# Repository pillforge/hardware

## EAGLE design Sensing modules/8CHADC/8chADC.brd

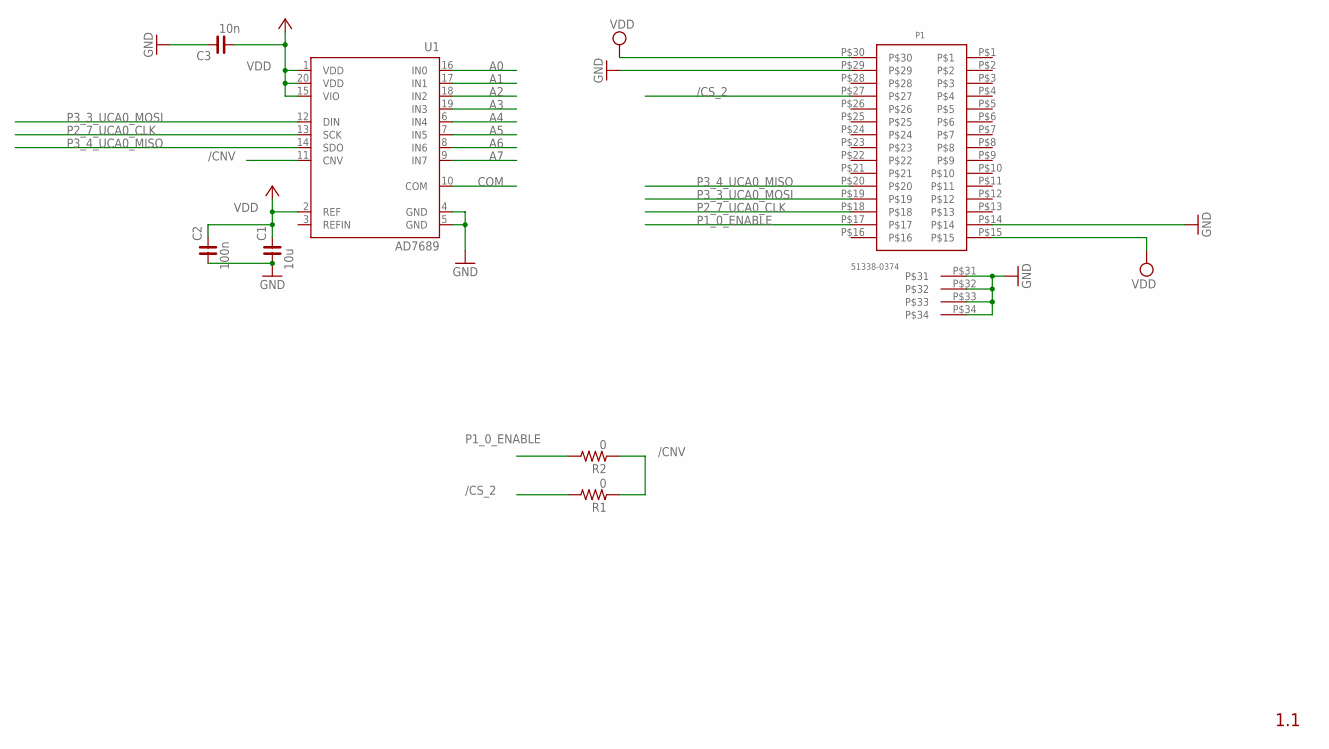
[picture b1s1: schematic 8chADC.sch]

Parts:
C1: 10u; C0402
C2: 100n; C0402
C3: 10n; C0402
P1: 51338-0374; 51338-0374_RECEPTACLE
R1, R2: 0; R0402
U1: AD7689; LFCSP20

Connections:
/CNV: R1.1, R2.1, U1.11 (CNV)
/CS_2: P1.P$27, R1.2
A0: U1.16 (IN0)
A1: U1.17 (IN1)
A2: U1.18 (IN2)
A3: U1.19 (IN3)
A4: U1.6 (IN4)
A5: U1.7 (IN5)
A6: U1.8 (IN6)
A7: U1.9 (IN7)
COM: U1.10 (COM)
GND: C1.1, C2.1, C3.2, P1.P$14, P1.P$29, P1.P$31, P1.P$32, P1.P$33, P1.P$34, U1.4 (GND), U1.5 (GND)
P1_0_ENABLE: P1.P$17, R2.2
P2_7_UCA0_CLK: P1.P$18, U1.13 (SCK)
P3_3_UCA0_MOSI: P1.P$19, U1.12 (DIN)
P3_4_UCA0_MISO: P1.P$20, U1.14 (SDO)
VDD: C1.2, C2.2, C3.1, P1.P$15, P1.P$30, U1.1 (VDD), U1.2 (REF), U1.15 (VIO), U1.20 (VDD)

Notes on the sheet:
1.1

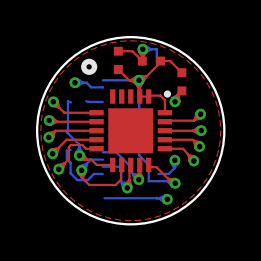
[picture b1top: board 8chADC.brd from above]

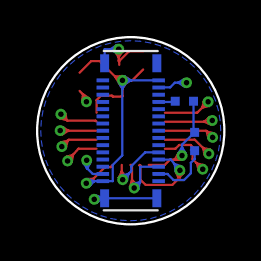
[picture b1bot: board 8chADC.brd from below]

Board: 2 copper layers, 10.4 x 10.4 mm, 7 parts (3 on the bottom side), 8 nets.

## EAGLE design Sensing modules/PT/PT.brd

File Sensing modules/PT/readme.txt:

XXXXXXXXXXXXXXXXXXXXXXXXXXXXXXXXXXXXXXXXXXXXXXXXXXXXXXXXXXXXXXXXXXXXXXXXXXXXX
X                                                                           X
X   Artwork and documentation done by: STORM LAB                            X
X                                                                           X
X   Company: VANDERBILT UNIVERSITY                                          X
XXXXXXXXXXXXXXXXXXXXXXXXXXXXXXXXXXXXXXXXXXXXXXXXXXXXXXXXXXXXXXXXXXXXXXXXXXXXX

PROJECT : PT
PCB NAME : PT
REVISION: 1.1 
DATE: 4-28-2015

PCB DESCRIPTION: 2 LAYER PCB 0.8 MM NOMINAL THICKNESS FR4
		Dimensions in mil (0.001 inch)
                            DOUBLE SIDE SOLDER MASK,
                            DOUBLE SIDE SILKSCREEN,
                            6 MIL MIN TRACE WIDTH AND 6 MIL MIN ISOLATION
		Dielectric constant for FR4 is 4.5

FILE NAME            		DESCRIPTION                               	FILE TYPE
-------------------------------------------------------------------------------------------
***PCB MANUFACTURING FILES:
PT.cmp				LAYER 1 COMPONENT SIDE/POSITIV              EXT. GERBER
PT.sol				LAYER 2 Inner layer/POSITIV                 EXT. GERBER

PT.stc				SOLDER MASK COMPONENT SIDE/NEGATIVE         EXT. GERBER
PT.stl				SOLDER MASK SOLDER SIDE/NEGATIVE            EXT. GERBER

PT.plc				SILKSCREEN COMPONENT SIDE/POSITIVE          EXT. GERBER
PT.pls				SILKSCREEN SOLDER SIDE/POSITIVE             EXT. GERBER

PT.crc				SOLDER PAST COMPONENT SIDE/POSITIVE         EXT. GERBER
PT.crs				SOLDER PAST SOLDER SIDE/POSITIVE            EXT. GERBER

PT.drd				DRILL/MECHANICAL DRAWING                    EXT. GERBER
PT.dri				DRILL/NC DRILL REPORT                       ASCII
PT.dim				BOARD OUTLINE             		    EXT. GERBER

PT_partlist.xls		PART LIST					    ASCII

***PDF FILES:
PT.PDF	Circuit Diagram

***EAGLE  FILES:
PT.SCH			Eagle 6.6 Schematic file
PT.BRD			Eagle 6.6 Layout file

README.TXT              THIS FILE                                   ASCII

***REVISION HISTORY

none

END.

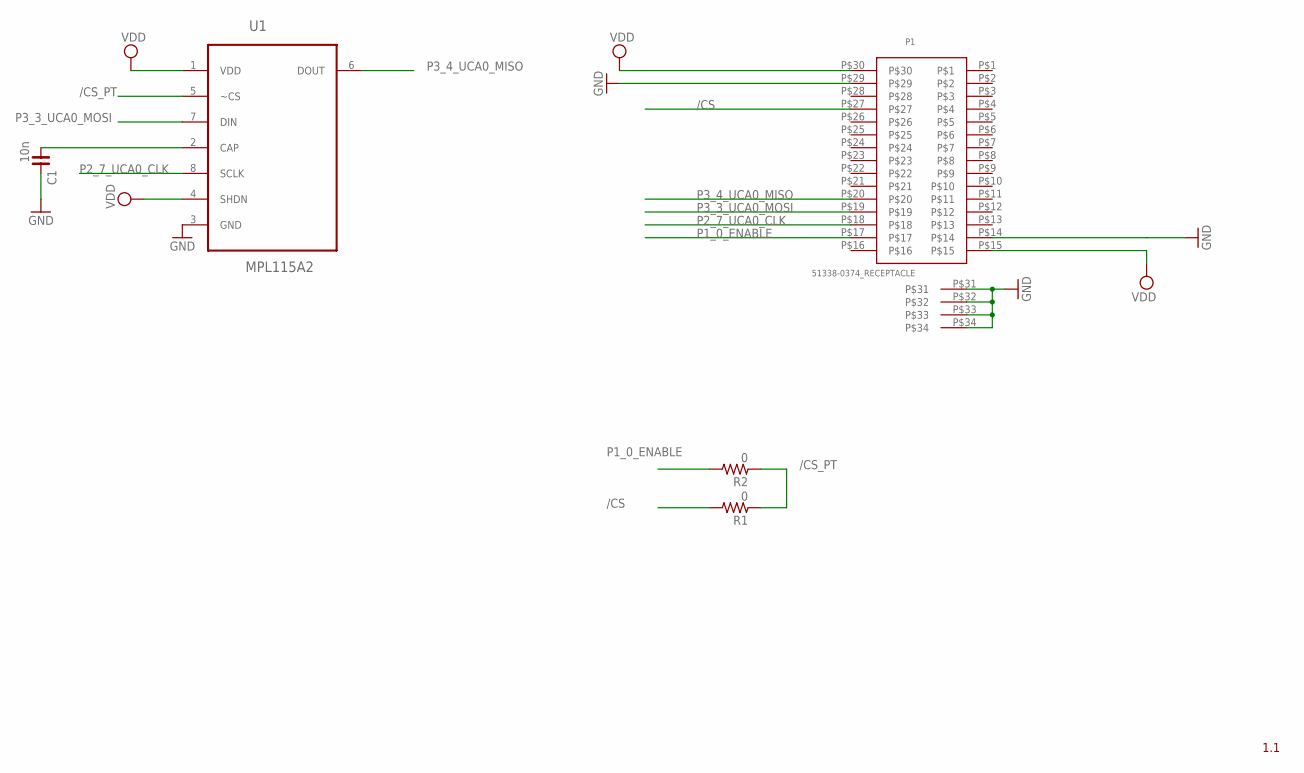
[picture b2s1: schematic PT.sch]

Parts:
C1: 10n; C0402
P1: 51338-0374_RECEPTACLE
R1, R2: 0; R0402
U1: MPL115A2; LGA8R125P0X4_500X300X120

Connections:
/CS: P1.P$27, R1.2
/CS_PT: R1.1, R2.1, U1.5 (~CS)
GND: C1.2, P1.P$14, P1.P$29, P1.P$31, P1.P$32, P1.P$33, P1.P$34, U1.3 (GND)
unnamed: C1.1, U1.2 (CAP)
P1_0_ENABLE: P1.P$17, R2.2
P2_7_UCA0_CLK: P1.P$18, U1.8 (SCLK)
P3_3_UCA0_MOSI: P1.P$19, U1.7 (DIN)
P3_4_UCA0_MISO: P1.P$20, U1.6 (DOUT)
VDD: P1.P$15, P1.P$30, U1.1 (VDD), U1.4 (SHDN)

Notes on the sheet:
1.1

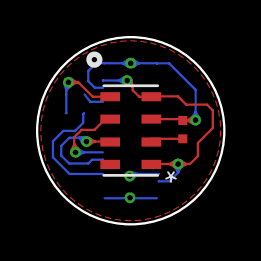
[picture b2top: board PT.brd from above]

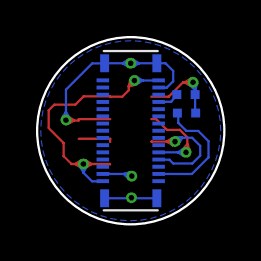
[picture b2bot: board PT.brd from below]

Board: 2 copper layers, 10.4 x 10.4 mm, 5 parts (3 on the bottom side), 9 nets.

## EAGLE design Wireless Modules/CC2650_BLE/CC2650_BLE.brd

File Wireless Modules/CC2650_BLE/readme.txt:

XXXXXXXXXXXXXXXXXXXXXXXXXXXXXXXXXXXXXXXXXXXXXXXXXXXXXXXXXXXXXXXXXXXXXXXXXXXXX
X                                                                           X
X   Artwork and documentation done by: STORM LAB                            X
X                                                                           X
X   Company: VANDERBILT UNIVERSITY                                          X
XXXXXXXXXXXXXXXXXXXXXXXXXXXXXXXXXXXXXXXXXXXXXXXXXXXXXXXXXXXXXXXXXXXXXXXXXXXXX

PROJECT : CC2650_BLE
PCB NAME : CC2650_BLE
REVISION: 1.1 
DATE: 4-28-2015

PCB DESCRIPTION: 2 LAYER PCB 0.8 MM NOMINAL THICKNESS FR4
		Dimensions in mil (0.001 inch)
                            DOUBLE SIDE SOLDER MASK,
                            DOUBLE SIDE SILKSCREEN,
                            6 MIL MIN TRACE WIDTH AND 6 MIL MIN ISOLATION
		Dielectric constant for FR4 is 4.5

FILE NAME            		DESCRIPTION                               	FILE TYPE
-------------------------------------------------------------------------------------------
***PCB MANUFACTURING FILES:
CC2650_BLE.cmp				LAYER 1 COMPONENT SIDE/POSITIV              EXT. GERBER
CC2650_BLE.sol				LAYER 2 Inner layer/POSITIV                 EXT. GERBER

CC2650_BLE.stc				SOLDER MASK COMPONENT SIDE/NEGATIVE         EXT. GERBER
CC2650_BLE.stl				SOLDER MASK SOLDER SIDE/NEGATIVE            EXT. GERBER

CC2650_BLE.plc				SILKSCREEN COMPONENT SIDE/POSITIVE          EXT. GERBER
CC2650_BLE.pls				SILKSCREEN SOLDER SIDE/POSITIVE             EXT. GERBER

CC2650_BLE.crc				SOLDER PAST COMPONENT SIDE/POSITIVE         EXT. GERBER
CC2650_BLE.crs				SOLDER PAST SOLDER SIDE/POSITIVE            EXT. GERBER

CC2650_BLE.drd				DRILL/MECHANICAL DRAWING                    EXT. GERBER
CC2650_BLE.dri				DRILL/NC DRILL REPORT                       ASCII

CC2650_BLE.dim				BOARD OUTLINE                      			EXT. GERBER

CC2650_BLE_partlist.xls		PART LIST									ASCII

***PDF FILES:
CC2650_BLE.PDF	Circuit Diagram

***EAGLE  FILES:
CC2650_BLE.SCH			Eagle 6.6 Schematic file
CC2650_BLE.BRD			Eagle 6.6 Layout file

README.TXT              THIS FILE                                   ASCII

***REVISION HISTORY

none

END.

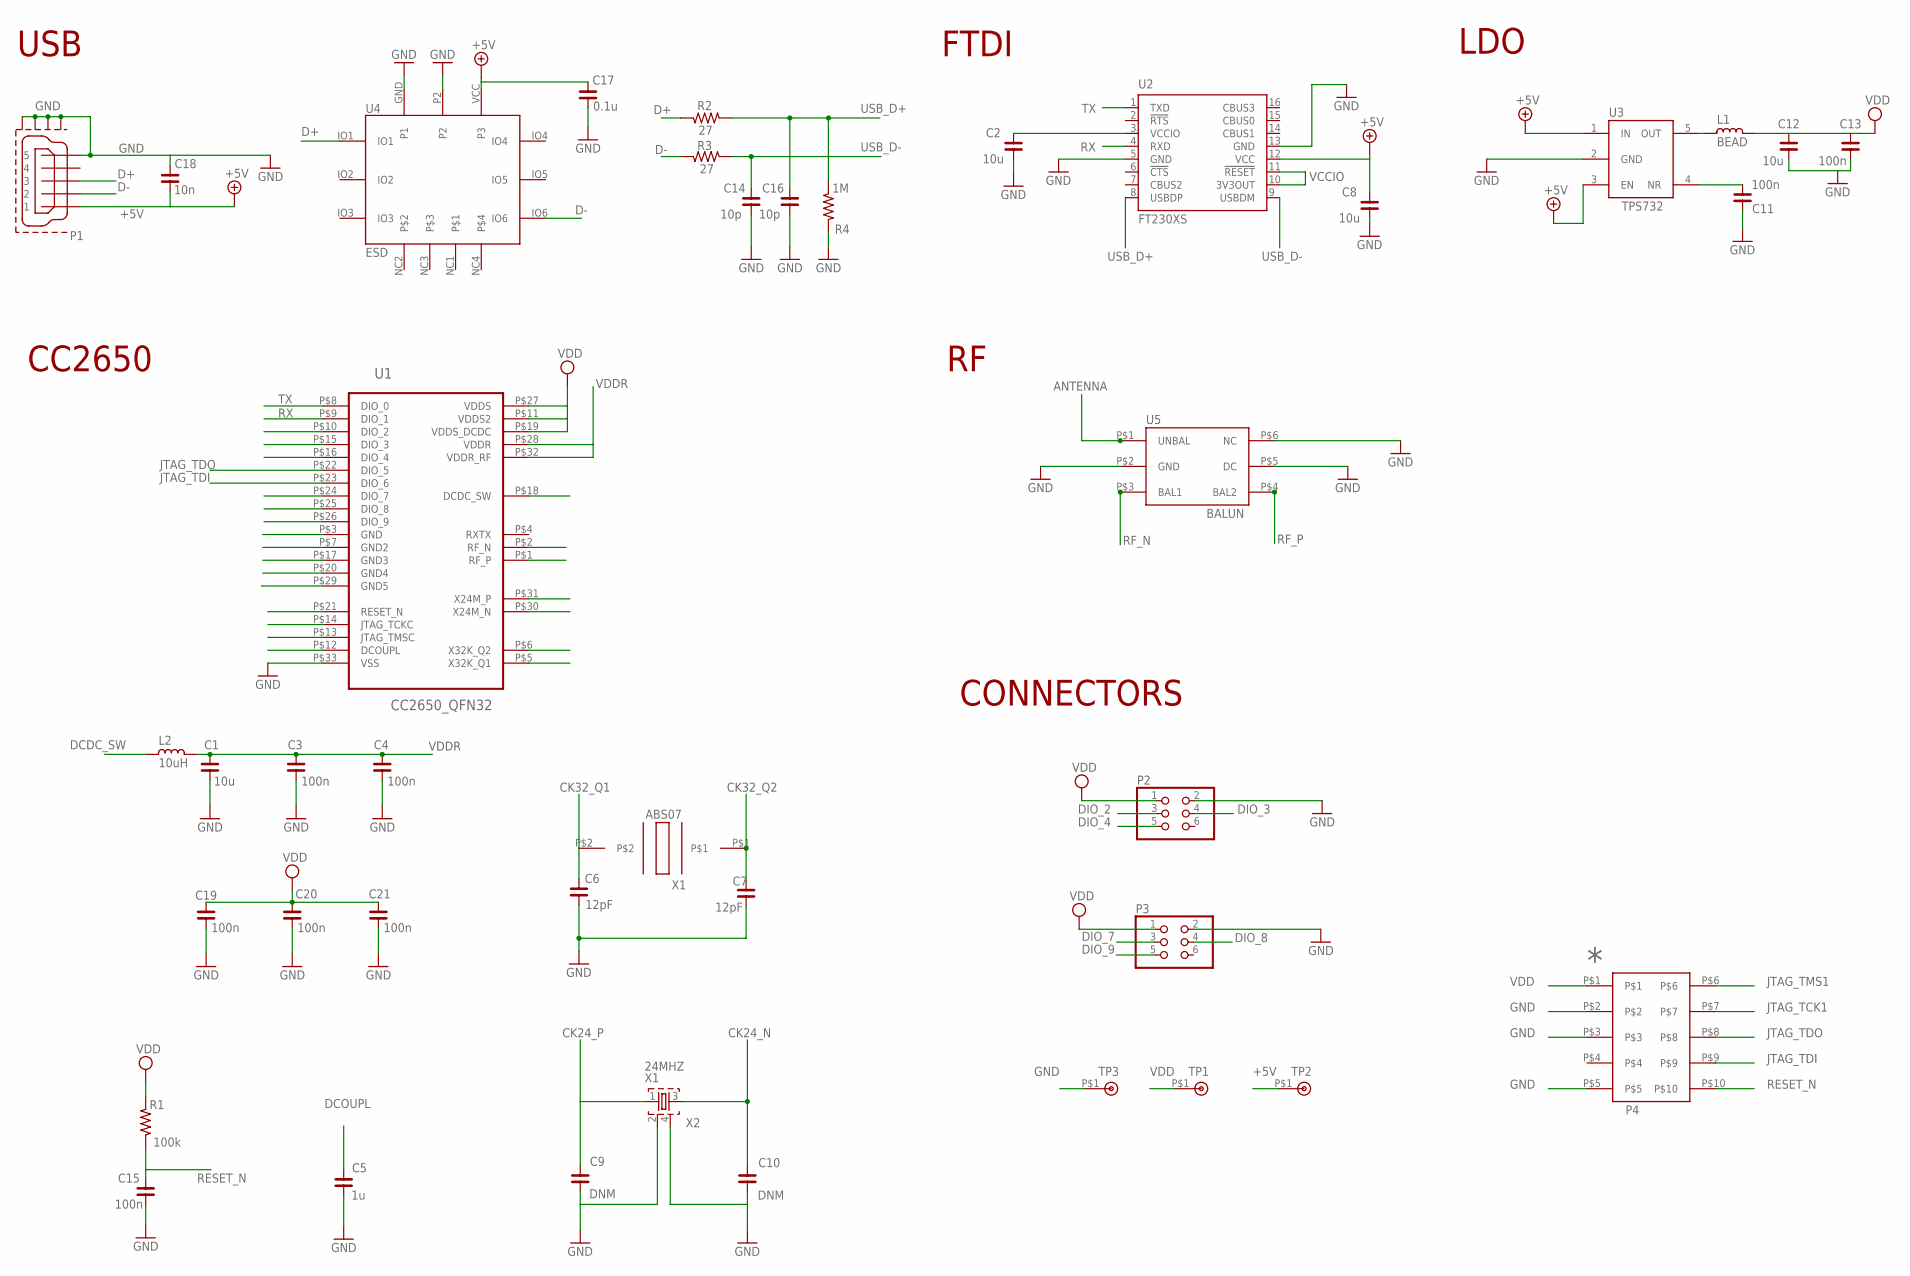
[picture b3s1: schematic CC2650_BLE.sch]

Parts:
24MHZ: X1; FA-20H
32KHZ: OSC32K; ABS07
C1, C2, C8, C12: 10u; C0402
C3, C4, C11, C13, C15, C19, C20, C21: 100n; C0402
C5: 1u; C0402
C6, C7: 12pF; C0402
C9, C10: DNM; C0402
C14, C16: 10p; C0402
C17: 0.1u; C0402
C18: 10n; C0402
L1: BEAD; L0402
L2: 10uH; L0402
P2, P3: PINHD-2X3; 2X03
R1: 100k; R0603
R2, R3: 27; R0603
R4: 1M; R0603
TP1: VDD; 5019_PAD
TP2: +5V; 5019_PAD
TP3: GND; 5019_PAD
U2: FT230XS; SSOP16
U3: TPS732XX; SOT23
U4: ESD
U5: BALUN_NRF8001; BALUNNORDIC
U$3: CC26504X4
U$5: FTSH-105-01-L-DV-K
USB: MINI-USB-SHIELD-UX60-MB-5ST; UX60-MB-5ST

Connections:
+3.3RAW: L1.2, U3.5 (OUT)
+5V: C8.2, C17.2, C18.1, TP2.P$1, U2.12 (VCC), U3.1 (IN), U3.3 (EN), U4.VCC (P3), USB.1
CK24_N: 24MHZ.3, C10.1, U$3.P$30 (X24M_N)
CK24_P: 24MHZ.1, C9.1, U$3.P$31 (X24M_P)
CK32_Q1: 32KHZ.P$2, C6.1, U$3.P$5 (X32K_Q1)
CK32_Q2: 32KHZ.P$1, C7.1, U$3.P$6 (X32K_Q2)
D+: R2.1, U4.IO1, USB.3; also elsewhere on the board
D-: R3.1, U4.IO6, USB.2; also elsewhere on the board
DCDC_SW: L2.2, U$3.P$18 (DCDC_SW)
DCOUPL: C5.2, U$3.P$12 (DCOUPL)
DIO_2: P2.3, U$3.P$10 (DIO_2)
DIO_3: P2.4, U$3.P$15 (DIO_3)
DIO_4: P2.5, U$3.P$16 (DIO_4)
DIO_7: P3.3, U$3.P$24 (DIO_7)
DIO_8: P3.4, U$3.P$25 (DIO_8)
DIO_9: P3.5, U$3.P$26 (DIO_9)
GND: 24MHZ.2, 24MHZ.4, C1.1, C2.1, C3.1, C4.1, C5.1, C6.2, C7.2, C8.1, C9.2, C10.2, C11.1, C12.1, C13.1, C14.1, C15.1, C16.1, C17.1, C18.2, C19.1, C20.1, C21.1, P2.2, P3.2, R4.2, TP3.P$1, U2.5 (GND), U2.13 (GND), U3.2 (GND), U4.GND (P1), U4.P2, U5.P$2 (GND), U5.P$5 (DC), U5.P$6 (NC), U$3.P$3 (GND), U$3.P$7 (GND2), U$3.P$17 (GND3), U$3.P$20 (GND4), U$3.P$33 (VSS), U$5.P$2, U$5.P$3, U$5.P$5, USB.5, USB.M1 (GND1), USB.M2 (GND2), USB.M3 (GND3), USB.M4 (GND4); also elsewhere on the board
JTAG_TCK1: U$3.P$14 (JTAG_TCKC), U$5.P$7
JTAG_TDI: U$3.P$23 (DIO_6), U$5.P$9
JTAG_TDO: U$3.P$22 (DIO_5), U$5.P$8
JTAG_TMS1: U$3.P$13 (JTAG_TMSC), U$5.P$6
unnamed: C11.2, U3.4 (NR)
RESET_N: C15.2, R1.1, U$3.P$21 (RESET_N), U$5.P$10
RF_N: U5.P$3 (BAL1), U$3.P$2 (RF_N); also elsewhere on the board
RF_P: U5.P$4 (BAL2), U$3.P$1 (RF_P); also elsewhere on the board
RX: U2.4 (RXD), U$3.P$9 (DIO_1)
TX: U2.1 (TXD), U$3.P$8 (DIO_0)
USB_D+: C16.2, R2.2, R4.1, U2.8 (USBDP); also elsewhere on the board
USB_D-: C14.2, R3.2, U2.9 (USBDM); also elsewhere on the board
VCCIO: C2.2, U2.3 (VCCIO), U2.10 (3V3OUT), U2.11 (!RESET)
VDD: C12.2, C13.2, C19.2, C20.2, C21.2, L1.1, P2.1, P3.1, R1.2, TP1.P$1, U$3.P$11 (VDDS2), U$3.P$19 (VDDS_DCDC), U$3.P$27 (VDDS), U$5.P$1
VDDR: C1.2, C3.2, C4.2, L2.1, U$3.P$28 (VDDR), U$3.P$32 (VDDR_RF)

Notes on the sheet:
USB
FTDI
LDO
CC2650
CONNECTORS

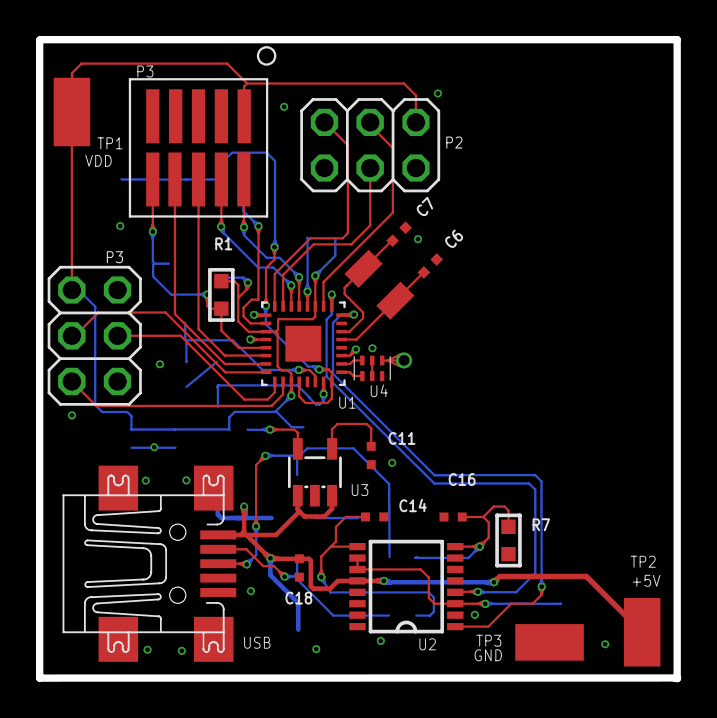
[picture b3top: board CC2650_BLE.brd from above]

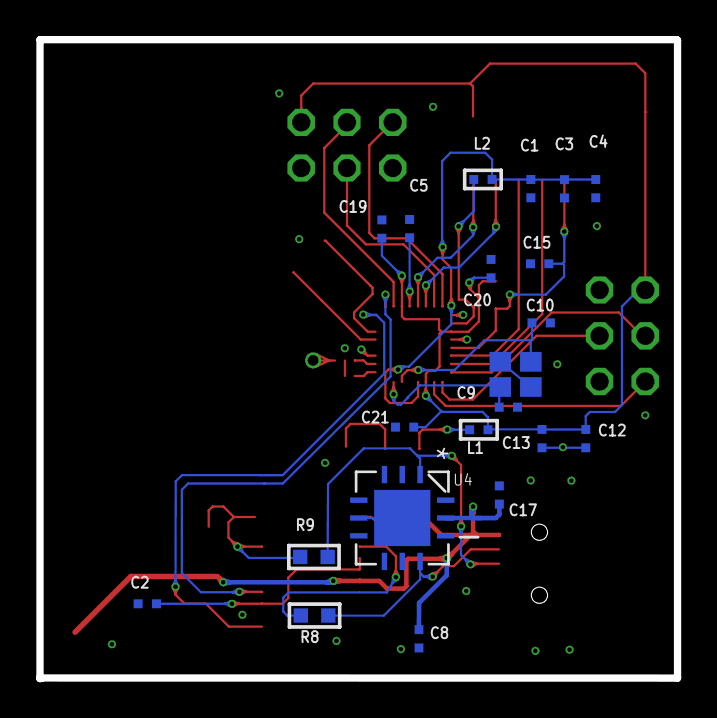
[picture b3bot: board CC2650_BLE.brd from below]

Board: 2 copper layers, 35.4 x 35.5 mm, 41 parts (21 on the bottom side), 32 nets.

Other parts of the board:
R7: 1M; R0603
R8, R9: 27; R0603
U1: BALUN_NRF8001; BALUNNORDIC

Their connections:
D+: R9.1; also elsewhere on the board
D-: R8.1; also elsewhere on the board
GND: R7.2, U1.P$2, U1.P$5, U1.P$6; also elsewhere on the board
RF_N: U1.P$3; also elsewhere on the board
RF_P: U1.P$4; also elsewhere on the board
USB_D+: R7.1, R9.2; also elsewhere on the board
USB_D-: R8.2; also elsewhere on the board

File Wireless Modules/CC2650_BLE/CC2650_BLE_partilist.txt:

CC2650F128RSM
UX60A-MB-5ST X1
5019KCT-ND X8
C17 10n
TPD6E001 RSF PACKAGE
R9 27
R8 27
C8 10p
C14 10p
R7 1M
FT230X
C2 10u
C22 10u
TPS732
C11 100n
L1 BEAD
C12 10u
C13 100n
L2 10uH
C1 10u
C3 100n
C4 100n
C19 100n
C20 100n
C21 100n
C6 12p
C7 12p
R1 100k
C15 100n
C5 1u
C8 1p
L7 2nH
ABS07-32.768KHZ-T ABRACON
TSX-3225 24.0000MF15X-AC3
BALUN LFB182G45BG5D920 MURATA
Headers & Wire Housings 2X20P DUAL ROW
Headers & Wire Housings 1X3P
TE CONNECTIVITY / AMP  5103308-2  WIRE-BOARD CONNECTOR, HEADER, 14 POSITION, 2.54MM

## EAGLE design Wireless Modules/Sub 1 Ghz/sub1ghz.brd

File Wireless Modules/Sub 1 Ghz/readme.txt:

XXXXXXXXXXXXXXXXXXXXXXXXXXXXXXXXXXXXXXXXXXXXXXXXXXXXXXXXXXXXXXXXXXXXXXXXXXXXX
X                                                                           X
X   Artwork and documentation done by: STORM LAB                            X
X                                                                           X
X   Company: VANDERBILT UNIVERSITY                                          X
XXXXXXXXXXXXXXXXXXXXXXXXXXXXXXXXXXXXXXXXXXXXXXXXXXXXXXXXXXXXXXXXXXXXXXXXXXXXX

PROJECT : sub1ghz
PCB NAME : sub1ghz
REVISION: 1.1 
DATE: 4-28-2015

PCB DESCRIPTION: 2 LAYER PCB 0.8 MM NOMINAL THICKNESS FR4
		Dimensions in mil (0.001 inch)
                            DOUBLE SIDE SOLDER MASK,
                            DOUBLE SIDE SILKSCREEN,
                            6 MIL MIN TRACE WIDTH AND 6 MIL MIN ISOLATION
		Dielectric constant for FR4 is 4.5

FILE NAME            		DESCRIPTION                               	FILE TYPE
-------------------------------------------------------------------------------------------
***PCB MANUFACTURING FILES:
sub1ghz.cmp				LAYER 1 COMPONENT SIDE/POSITIV              EXT. GERBER
sub1ghz.sol				LAYER 2 Inner layer/POSITIV                 EXT. GERBER

sub1ghz.stc				SOLDER MASK COMPONENT SIDE/NEGATIVE         EXT. GERBER
sub1ghz.stl				SOLDER MASK SOLDER SIDE/NEGATIVE            EXT. GERBER

sub1ghz.plc				SILKSCREEN COMPONENT SIDE/POSITIVE          EXT. GERBER
sub1ghz.pls				SILKSCREEN SOLDER SIDE/POSITIVE             EXT. GERBER

sub1ghz.crc				SOLDER PAST COMPONENT SIDE/POSITIVE         EXT. GERBER
sub1ghz.crs				SOLDER PAST SOLDER SIDE/POSITIVE            EXT. GERBER

sub1ghz.drd				DRILL/MECHANICAL DRAWING                    EXT. GERBER
sub1ghz.dri				DRILL/NC DRILL REPORT                       ASCII

sub1ghz.dim				BOARD OUTLINE                      			EXT. GERBER

sub1ghz_partlist.xls		PART LIST									ASCII

***PDF FILES:
sub1ghz.PDF	Circuit Diagram

***EAGLE  FILES:
sub1ghz.SCH			Eagle 6.6 Schematic file
sub1ghz.BRD			Eagle 6.6 Layout file

README.TXT              THIS FILE                                   ASCII

***REVISION HISTORY

none

END.

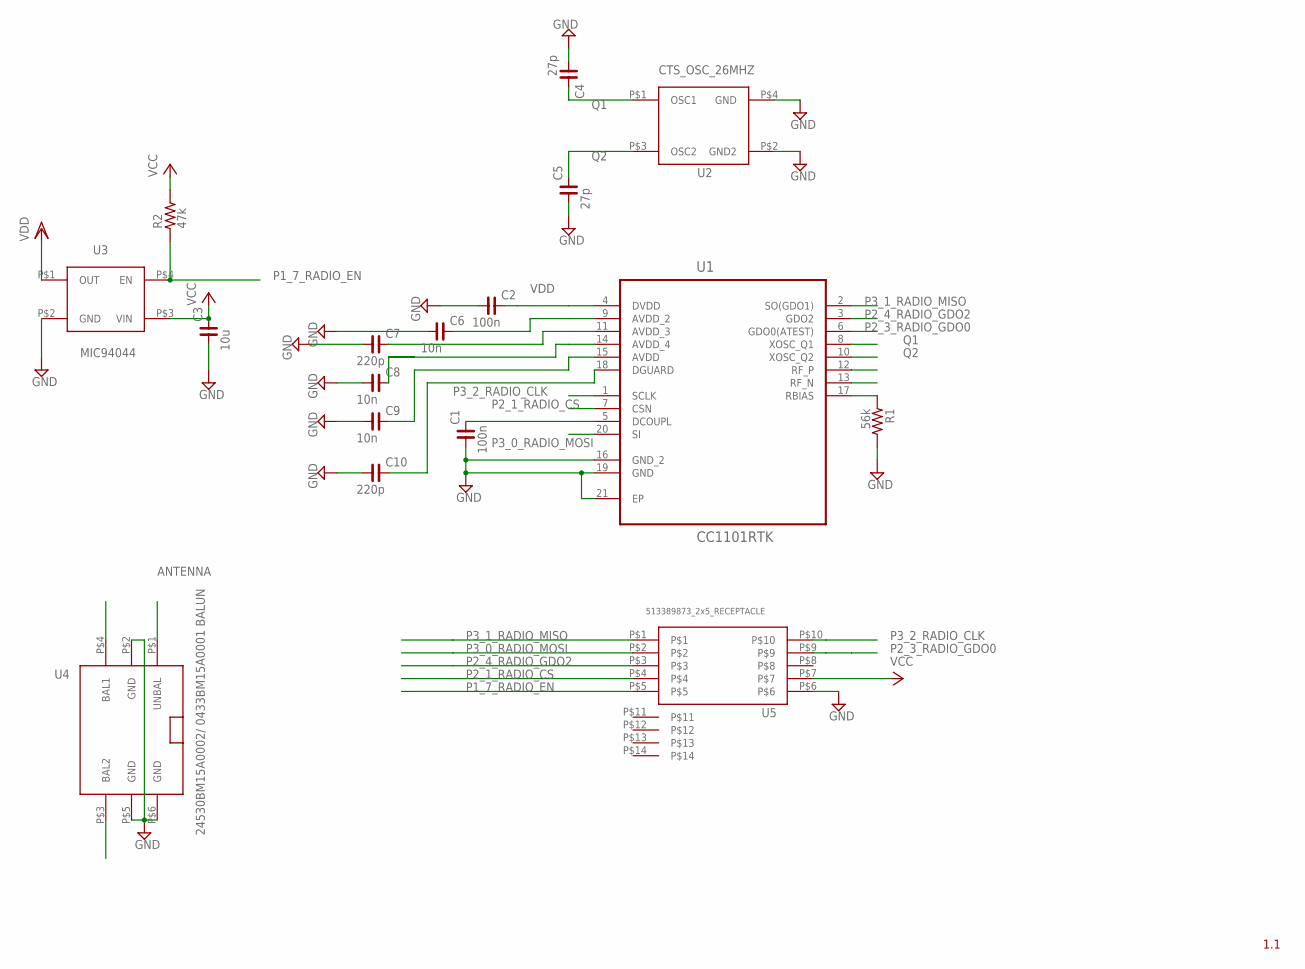
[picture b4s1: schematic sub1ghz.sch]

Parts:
C1, C2: 100n; C0402
C3: 10u; C0402
C4, C5: 27p; C0402
C6, C8, C9: 10n; C0402
C7, C10: 220p; C0402
R1: 56k; R0402
R2: 47k; R0402
U1: CC1101RTK; QFN50P400X400X90-21N
U$1: 26_MHZ_OSC; CTS_26_PACKAGE
U$2: MIC94044; MIC94045YFL_FOOTPRINT
U$3: 24530BM15A0002
U$4: 513389873_2X5_RECEPTACLE

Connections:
ANTENNA: U$3.P$1 (UNBAL)
GND: C1.1, C2.1, C3.1, C4.1, C5.1, C6.1, C7.1, C8.1, C9.1, C10.1, R1.2, U1.16 (GND_2), U1.19 (GND), U1.21 (EP), U$1.P$2 (GND2), U$1.P$4 (GND), U$2.P$2 (GND), U$3.P$2 (GND), U$3.P$5 (GND), U$3.P$6 (GND), U$4.P$6
unnamed: U1.12 (RF_P), U$3.P$4 (BAL1)
unnamed: U1.13 (RF_N), U$3.P$3 (BAL2)
unnamed: R1.1, U1.17 (RBIAS)
unnamed: C1.2, U1.5 (DCOUPL)
P1_7_RADIO_EN: R2.1, U$2.P$4 (EN), U$4.P$5
P2_1_RADIO_CS: U1.7 (CSN), U$4.P$4
P2_3_RADIO_GDO0: U1.6 (GDO0(ATEST)), U$4.P$9
P2_4_RADIO_GDO2: U1.3 (GDO2), U$4.P$3
P3_0_RADIO_MOSI: U1.20 (SI), U$4.P$2
P3_1_RADIO_MISO: U1.2 (SO(GDO1)), U$4.P$1
P3_2_RADIO_CLK: U1.1 (SCLK), U$4.P$10
Q1: C4.2, U1.8 (XOSC_Q1), U$1.P$1 (OSC1)
Q2: C5.2, U1.10 (XOSC_Q2), U$1.P$3 (OSC2)
VCC: C3.2, R2.2, U$2.P$3 (VIN), U$4.P$7
VDD: C2.2, C6.2, C7.2, C8.2, C9.2, C10.2, U1.4 (DVDD), U1.9 (AVDD_2), U1.11 (AVDD_3), U1.14 (AVDD_4), U1.15 (AVDD), U1.18 (DGUARD), U$2.P$1 (OUT)

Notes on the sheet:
1.1

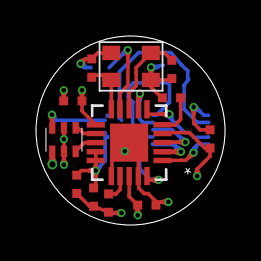
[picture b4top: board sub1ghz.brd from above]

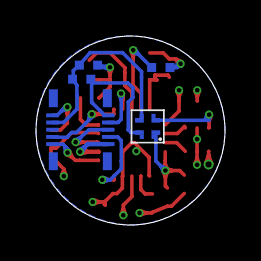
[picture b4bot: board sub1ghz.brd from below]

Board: 4 copper layers, 10.5 x 10.5 mm, 17 parts (5 on the bottom side), 16 nets.

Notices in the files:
parts and their libraries:
rc-master-smd: Copyright (C) 2007, Bob Starr
